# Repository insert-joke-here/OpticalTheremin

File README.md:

# OpticalTheremin

This is an optical theremin using the esp-32 based microcontroller LILYGO T7-S3. A theremin is an instrument where it is not touched while playing, instead sensing the position of the player's hand in the air. A normal theremin uses electromagnetic fields and capacitance to detect the player's hand, while this theremin instead uses a distance sensor to detect the position. While this provides much less sensitivity, it is more straightforward to implement and relatively software dependent. The sensor used here is an Adafruit VL6180X. An optical sensor is used over the more typical ultrasound detectors because of the better precision that the optical sensor provides, and its tighter cone, to protect it from undesired interference. 

It uses three sliders, one for the volume, one for the sensitivity (which determines the pitch), and one for the vibrato, which makes the instrument sound less dry. This vibrato is done by using a sine wave that centers around the desired pitch, whose amplitude is defined by the slider. 

Since this theremin uses an actual speaker over a buzzer, it requires an amplifier, which here is the Adafruit MAX98357 breakout board.

Schematic:

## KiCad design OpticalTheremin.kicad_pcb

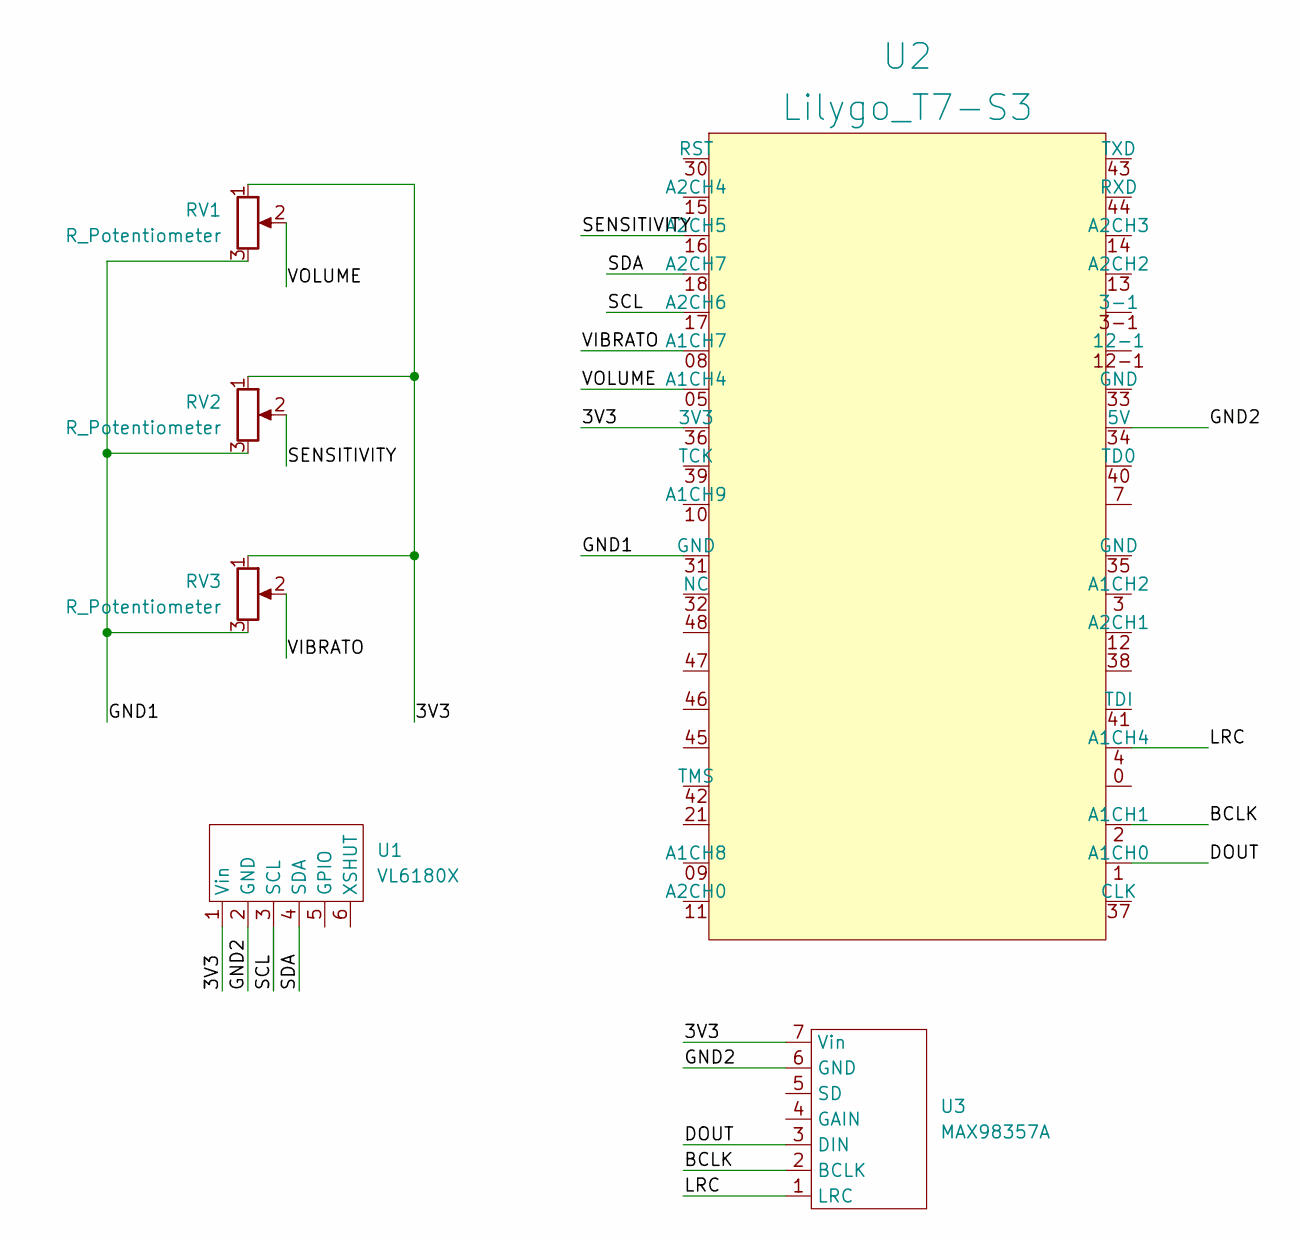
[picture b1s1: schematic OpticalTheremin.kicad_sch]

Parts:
RV1, RV2, RV3: R_Potentiometer; Potentiometer_Bourns_PTA1543_Single_Slide
U1: VL6180X
U2: Lilygo_T7-S3; LilyGo_T7-S3
U3: MAX98357A

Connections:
/3V3: RV1.1, RV2.1, RV3.1, U1.1 (Vin), U2.36 (3V3), U3.7 (Vin)
/BCLK: U2.2 (A1CH1), U3.2 (BCLK)
/DOUT: U2.1 (A1CH0), U3.3 (DIN)
/GND1: RV1.3, RV2.3, RV3.3, U2.31 (GND)
/GND2: U1.2 (GND), U2.34 (5V), U3.6 (GND)
/LRC: U2.4 (A1CH4), U3.1 (LRC)
/SCL: U1.3 (SCL), U2.17 (A2CH6)
/SDA: U1.4 (SDA), U2.18 (A2CH7)
/SENSITIVITY: RV2.2, U2.16 (A2CH5)
/VIBRATO: RV3.2, U2.08 (A1CH7)
/VOLUME: RV1.2, U2.05 (A1CH4)

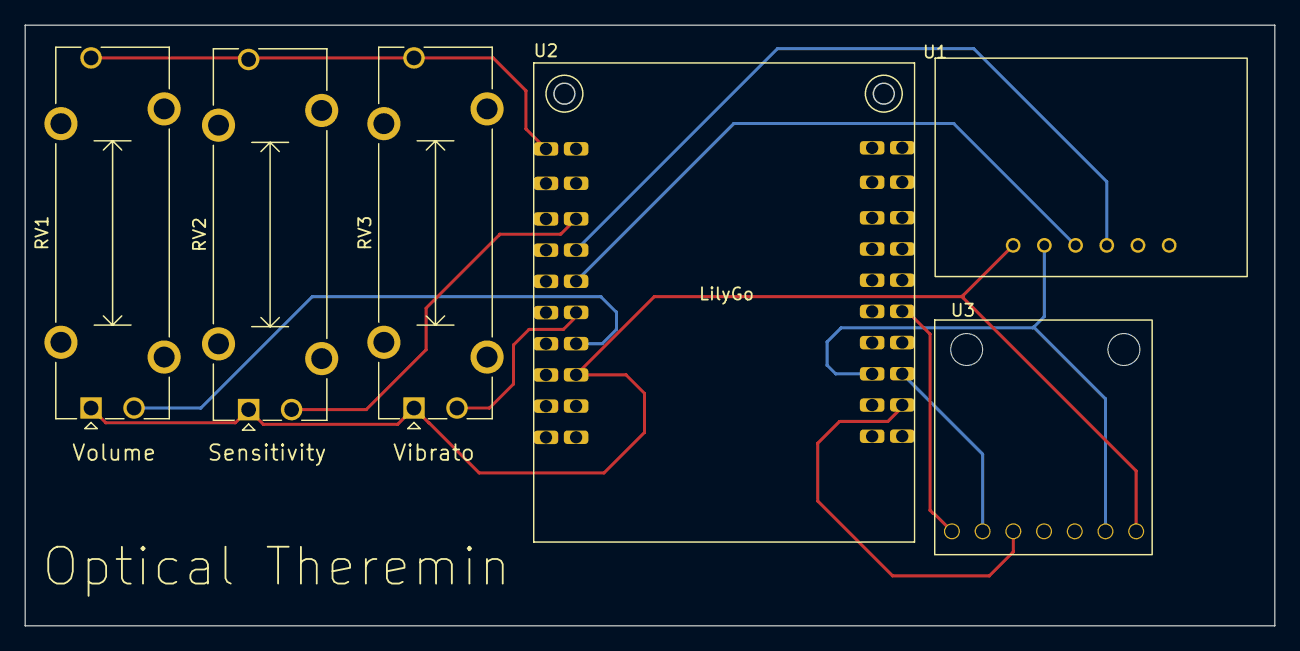
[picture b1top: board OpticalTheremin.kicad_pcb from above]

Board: 2 copper layers, 101.7 x 48.9 mm, 6 parts (0 on the bottom side), 11 nets.

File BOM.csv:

Item,Qty,Supplier,Cost/item,Total Cost,link
VL6180X ToF Distance Sensor,1,Digikey,$13.95,$13.95,https://www.digikey.com/en/products/detail/adafruit-industri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
MAX98357A Amplifier,1,Adafruit,$5.95,$5.95,https://www.adafruit.com/product/3006
Mono Speaker,1,Adafruit,$3.95,$3.95,https://www.adafruit.com/product/4445
LILYGO T7-S3,1,Lilygo,$7.93,$7.93,https://lilygo.cc/products/t7-s3
PCB board,1,JLCPCB,$11.44,$11.44,https://jlcpcb.com
Potentiometers,3,Digikey,$1.84,$5.52,https://www.digikey.com/en/products/detail/bourns-inc/PTA154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
Estimated total shipping,1,,,$6.90,
